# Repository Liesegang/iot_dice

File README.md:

# IoT Dice

IoT Diceは、サイコロの姿勢をBluetooth Low Energyでブラウザへ送り、3Dのサイコロとして表示するプロジェクトです。
nRF5340とBNO085から取得した姿勢情報を、Web Bluetooth対応のWebアプリで可視化します。

Webアプリは[GitHub Pages](https://liesegang.github.io/iot_dice/)で公開しています。

## 動作モード

通常は姿勢共有モードで動作します。
サイコロから約50 Hzで姿勢情報だけを送り、ブラウザ上の3D表示へ反映します。

Webアプリで「シミュレーション」を有効にすると、投擲状態、衝撃、出目などの情報も送信します。
このモードでは、Rapierを使ったモンテカルロシミュレーションによる出目予測と、計測データの記録・書き出しを利用できます。

## ディレクトリ構成

```text
firmware/  nRF5340用ファームウェア
software/  Web Bluetooth対応Webアプリ
hardware/  基板データと回路図
```

## ファームウェア

### 必要なもの

- nRF Connect SDK 3.4.0
- nRF5340 DK
- BNO085

nRF Connect SDKのターミナルで、リポジトリのルートから次のコマンドを実行します。

```sh
west build -b nrf5340dk/nrf5340/cpuapp --sysbuild -d firmware/build firmware
west flash -d firmware/build
```

`--sysbuild`により、nRF5340のネットワークコア用`hci_ipc`も同時にビルドされます。
VS CodeのnRF Connect拡張機能を使う場合は、アプリケーションのディレクトリに`firmware`を指定してください。

## Webアプリ

```sh
cd software
npm ci
npm run dev
```

配布用ファイルは次のコマンドで生成します。

```sh
npm run build
```

Web Bluetoothを利用するため、ChromeまたはEdgeでHTTPSのページ、もしくは`localhost`を開いてください。
ページ上の接続ボタンから、Bluetoothデバイス名`dice`を選択します。

## ハードウェア

基板データは`hardware/iot_dice.brd`、回路図は`hardware/iot_dice.sch`にあります。

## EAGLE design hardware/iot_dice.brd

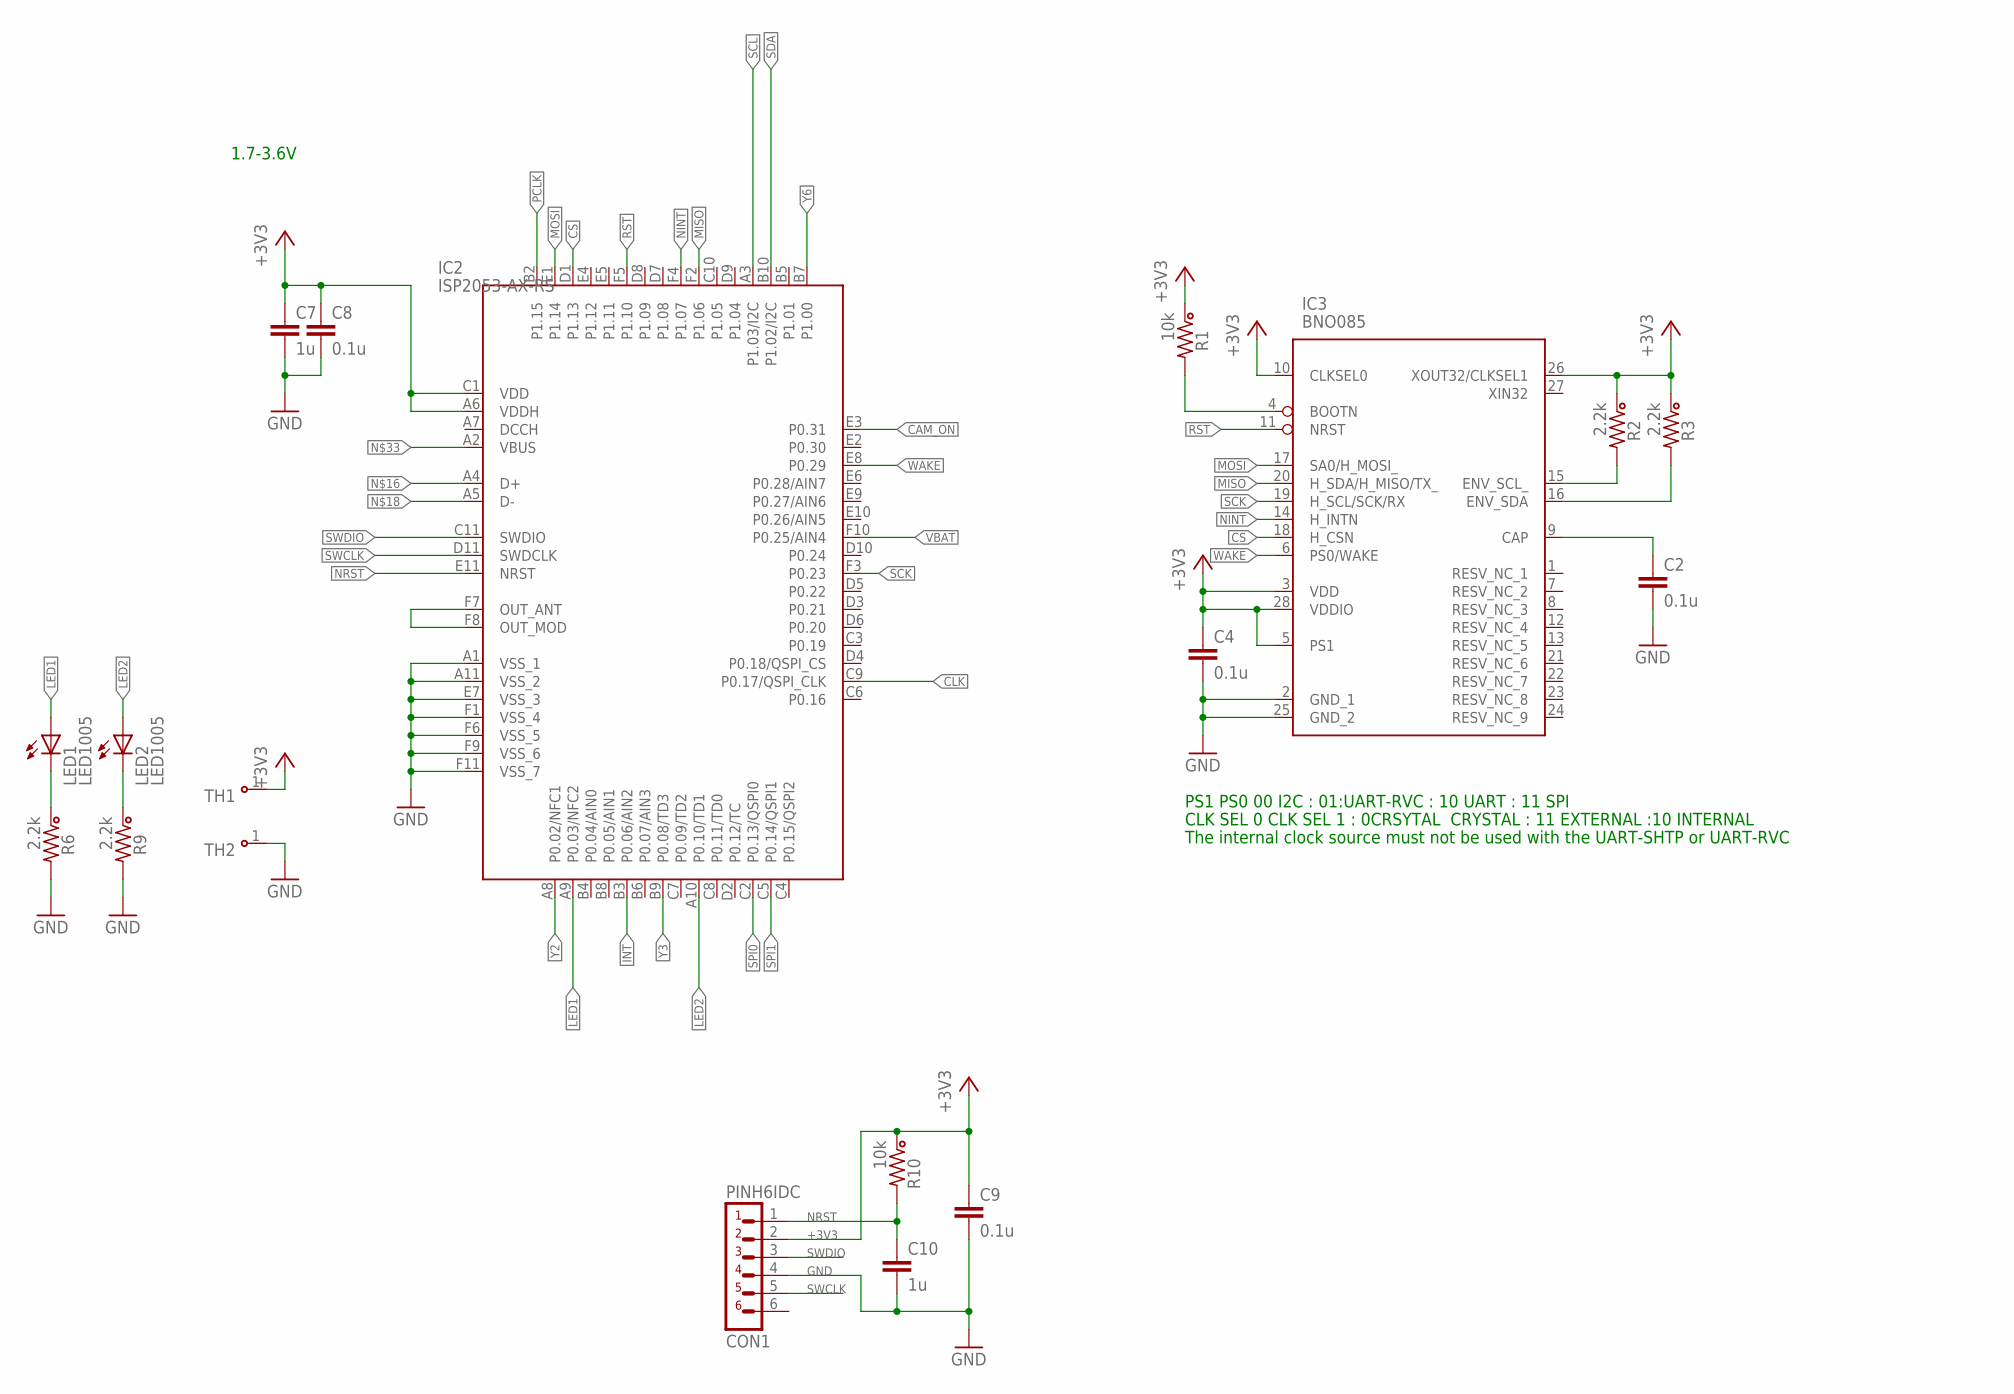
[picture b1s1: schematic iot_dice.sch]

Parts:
C2, C4, C8, C9: 0.1u; 1005K
C7, C10: 1u; 1005K
CON1: PINH6IDC; 1X6IDC_1R27
IC2: ISP2053-AX-RS; ISP2053AXRS
IC3: BNO085
LED1, LED2: LED1005; 1005K-LED
R1, R10: 10k; 1005K
R2, R3, R6, R9: 2.2k; 1005K
TH1, TH2: THCHK; 03C

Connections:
+3V3: C4.1, C7.1, C8.1, C9.1, CON1.2, IC2.A6 (VDDH), IC2.C1 (VDD), IC3.3 (VDD), IC3.5 (PS1), IC3.10 (CLKSEL0), IC3.26 (XOUT32/CLKSEL1), IC3.28 (VDDIO), R1.1, R2.1, R3.1, R10.1, TH1.1
CAM_ON: IC2.E3 (P0.31)
CLK: IC2.C9 (P0.17/QSPI_CLK)
CS: IC2.D1 (P1.13), IC3.18 (H_CSN)
GND: C2.2, C4.2, C7.2, C8.2, C9.2, C10.2, CON1.4, IC2.A1 (VSS_1), IC2.A11 (VSS_2), IC2.E7 (VSS_3), IC2.F1 (VSS_4), IC2.F6 (VSS_5), IC2.F9 (VSS_6), IC2.F11 (VSS_7), IC3.2 (GND_1), IC3.25 (GND_2), R6.2, R9.2, TH2.1
INT: IC2.B3 (P0.06/AIN2)
LED1: IC2.A9 (P0.03/NFC2), LED1.A
LED2: IC2.A10 (P0.10/TD1), LED2.A
MISO: IC2.F2 (P1.06), IC3.20 (H_SDA/H_MISO/TX_)
MOSI: IC2.E1 (P1.14), IC3.17 (SA0/H_MOSI_)
unnamed: LED2.K (C), R9.1
unnamed: IC2.F7 (OUT_ANT), IC2.F8 (OUT_MOD)
unnamed: LED1.K (C), R6.1
unnamed: C2.1, IC3.9 (CAP)
unnamed: IC3.4 (BOOTN), R1.2
unnamed: IC3.15 (ENV_SCL_), R2.2
unnamed: IC3.16 (ENV_SDA), R3.2
NINT: IC2.F4 (P1.07), IC3.14 (H_INTN)
NRST: C10.1, CON1.1, IC2.E11 (NRST), R10.2
PCLK: IC2.B2 (P1.15)
RST: IC2.F5 (P1.10), IC3.11 (NRST)
SCK: IC2.F3 (P0.23), IC3.19 (H_SCL/SCK/RX)
SCL: IC2.A3 (P1.03/I2C)
SDA: IC2.B10 (P1.02/I2C)
SPI0: IC2.C2 (P0.13/QSPI0)
SPI1: IC2.C5 (P0.14/QSPI1)
SWCLK: CON1.5, IC2.D11 (SWDCLK)
SWDIO: CON1.3, IC2.C11 (SWDIO)
VBAT: IC2.F10 (P0.25/AIN4)
WAKE: IC2.E8 (P0.29), IC3.6 (PS0/WAKE)
Y2: IC2.A8 (P0.02/NFC1)
Y3: IC2.B9 (P0.08/TD3)
Y6: IC2.B7 (P1.00)

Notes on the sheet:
1.7-3.6V
PS1 PS0 00 I2C : 01:UART-RVC : 10 UART : 11 SPI
CLK SEL 0 CLK SEL 1 : 0CRSYTAL CRYSTAL : 11 EXTERNAL :10 INTERNAL
The internal clock source must not be used with the UART-SHTP or UART-RVC

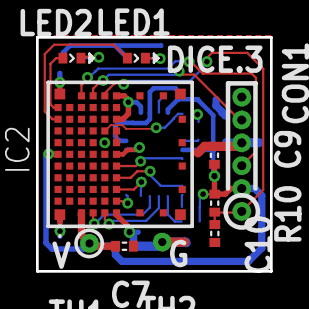
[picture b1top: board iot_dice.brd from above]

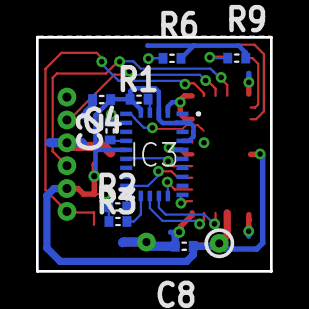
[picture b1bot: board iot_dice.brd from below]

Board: 2 copper layers, 13.0 x 13.0 mm, 19 parts (9 on the bottom side), 21 nets.

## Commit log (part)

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2026-06-09 Initial commit for dice-test2
2026-06-09 Refactor to C++: BNO085 driver class with GPIO interrupt, module split
